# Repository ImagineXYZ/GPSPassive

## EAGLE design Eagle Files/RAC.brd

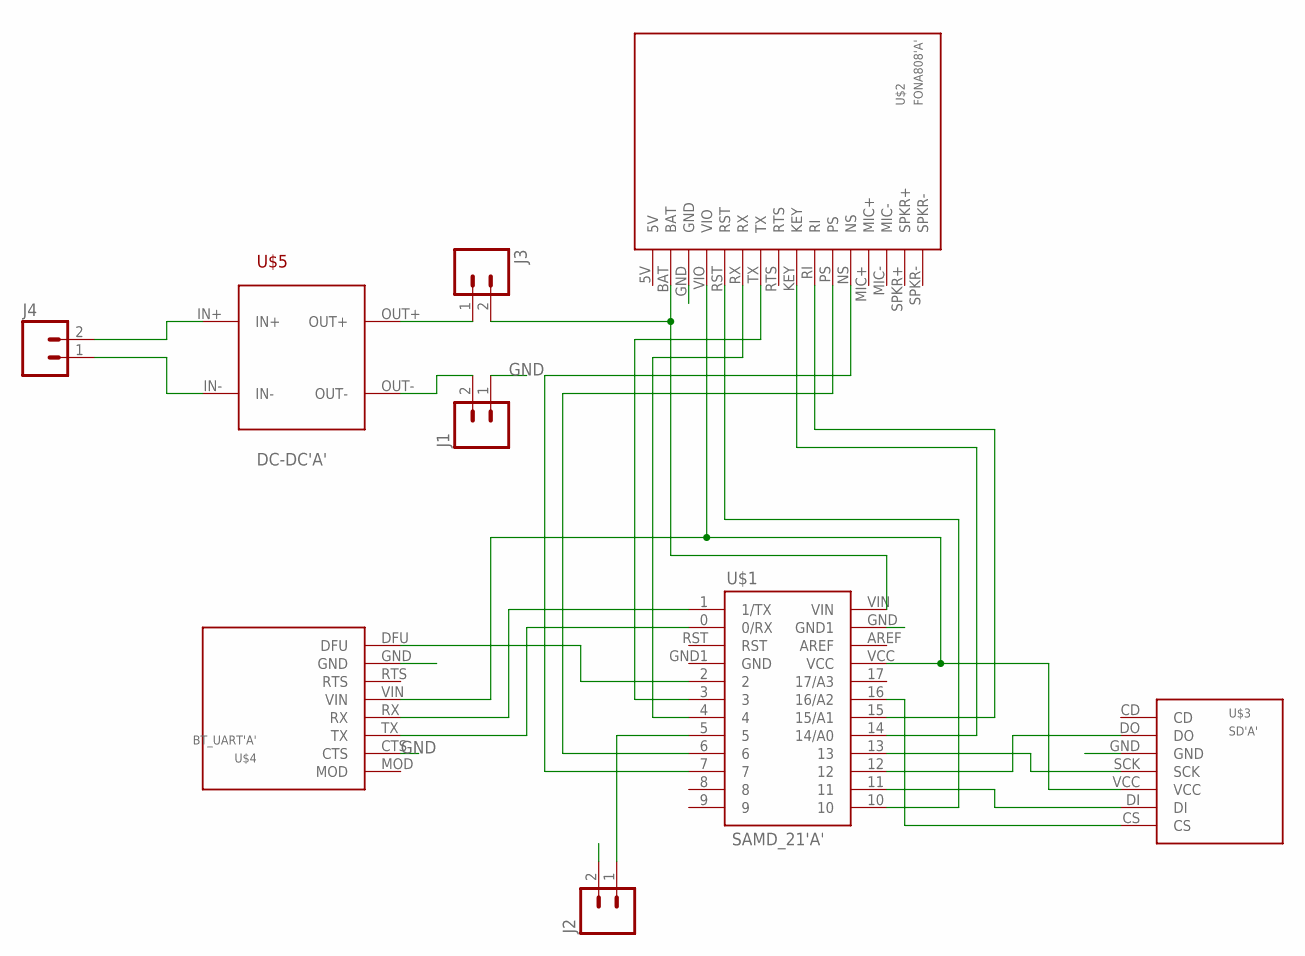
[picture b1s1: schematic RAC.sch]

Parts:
J1, J2, J3: M02PTH; 1X02
J4: M025MM; SCREWTERMINAL-5MM-2
U$1: SAMD_21'A'; MINI
U$2: FONA808'A'; FONA
U$3: SD'A'; SD_BR
U$4: BT_UART'A'; BLE
U$5: DC-DC'A'; DC-DC

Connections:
GND: J1.1, J2.2, U$1.GND (GND1), U$1.GND1 (GND), U$2.GND, U$3.GND, U$4.CTS, U$4.GND
unnamed: J3.2, U$1.VIN, U$2.BAT
unnamed: U$1.4, U$2.RX
unnamed: U$1.3, U$2.TX
unnamed: U$1.VCC, U$2.VIO, U$3.VCC, U$4.VIN
unnamed: U$1.14 (14/A0), U$2.KEY
unnamed: U$1.15 (15/A1), U$2.RI
unnamed: U$1.10, U$2.RST
unnamed: U$1.11, U$3.DI
unnamed: U$1.12, U$3.DO
unnamed: U$1.13, U$3.SCK
unnamed: U$1.16 (16/A2), U$3.CS
unnamed: U$1.0 (0/RX), U$4.TX
unnamed: U$1.2, U$4.DFU
unnamed: J3.1, U$5.OUT+
unnamed: J1.2, U$5.OUT-
unnamed: J4.2, U$5.IN+
unnamed: J4.1, U$5.IN-
S$1: J2.1, U$1.5
S$2: U$1.6, U$2.PS
S$3: U$1.7, U$2.NS
S$4: U$1.1 (1/TX), U$4.RX

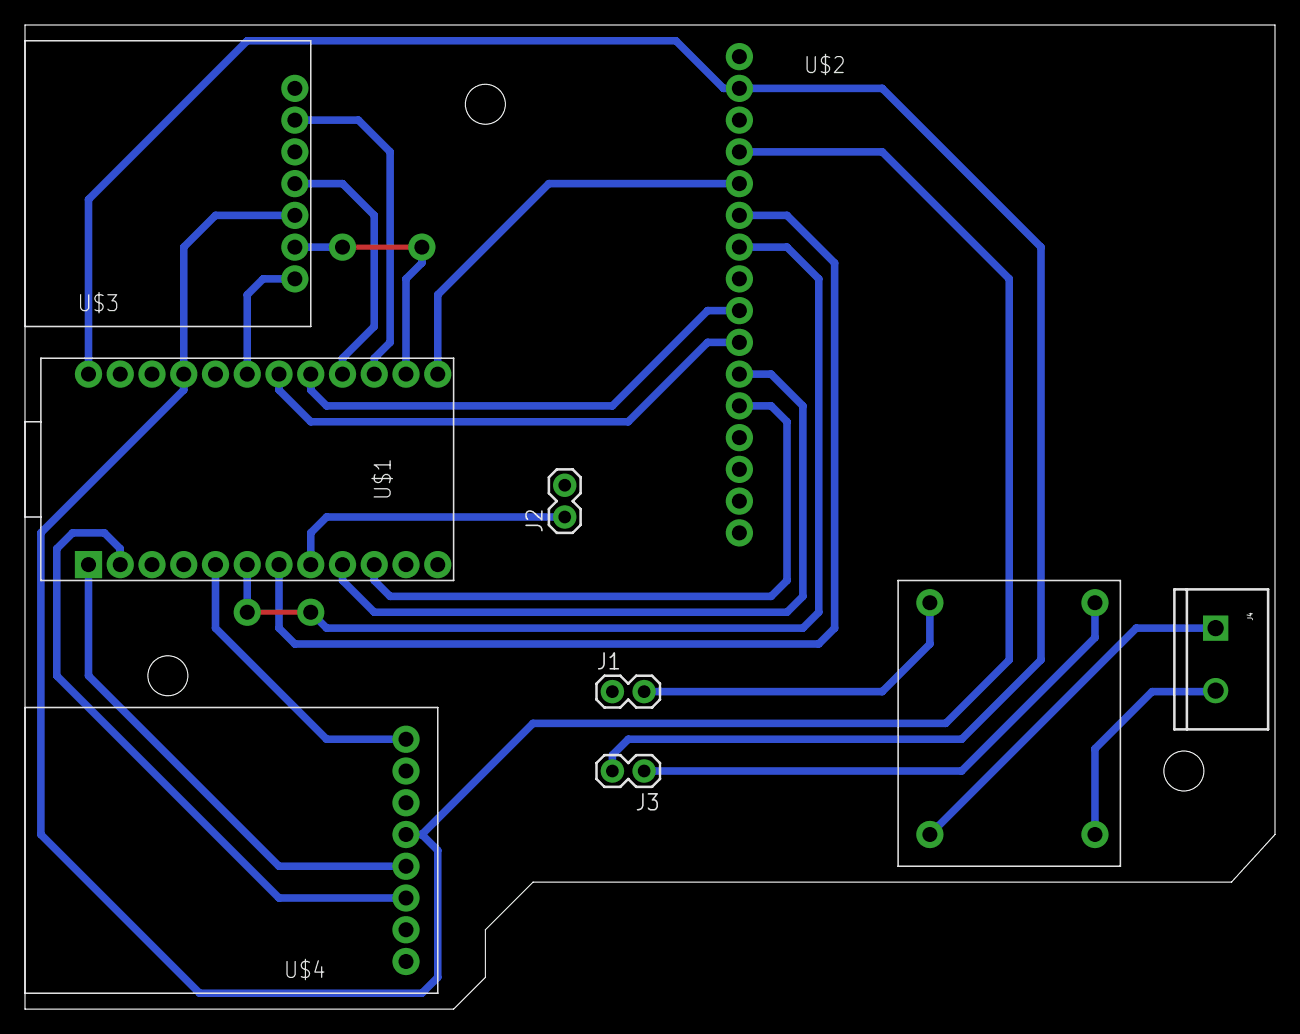
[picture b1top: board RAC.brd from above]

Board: 2 copper layers, 100.0 x 78.7 mm, 9 parts (0 on the bottom side), 22 nets.

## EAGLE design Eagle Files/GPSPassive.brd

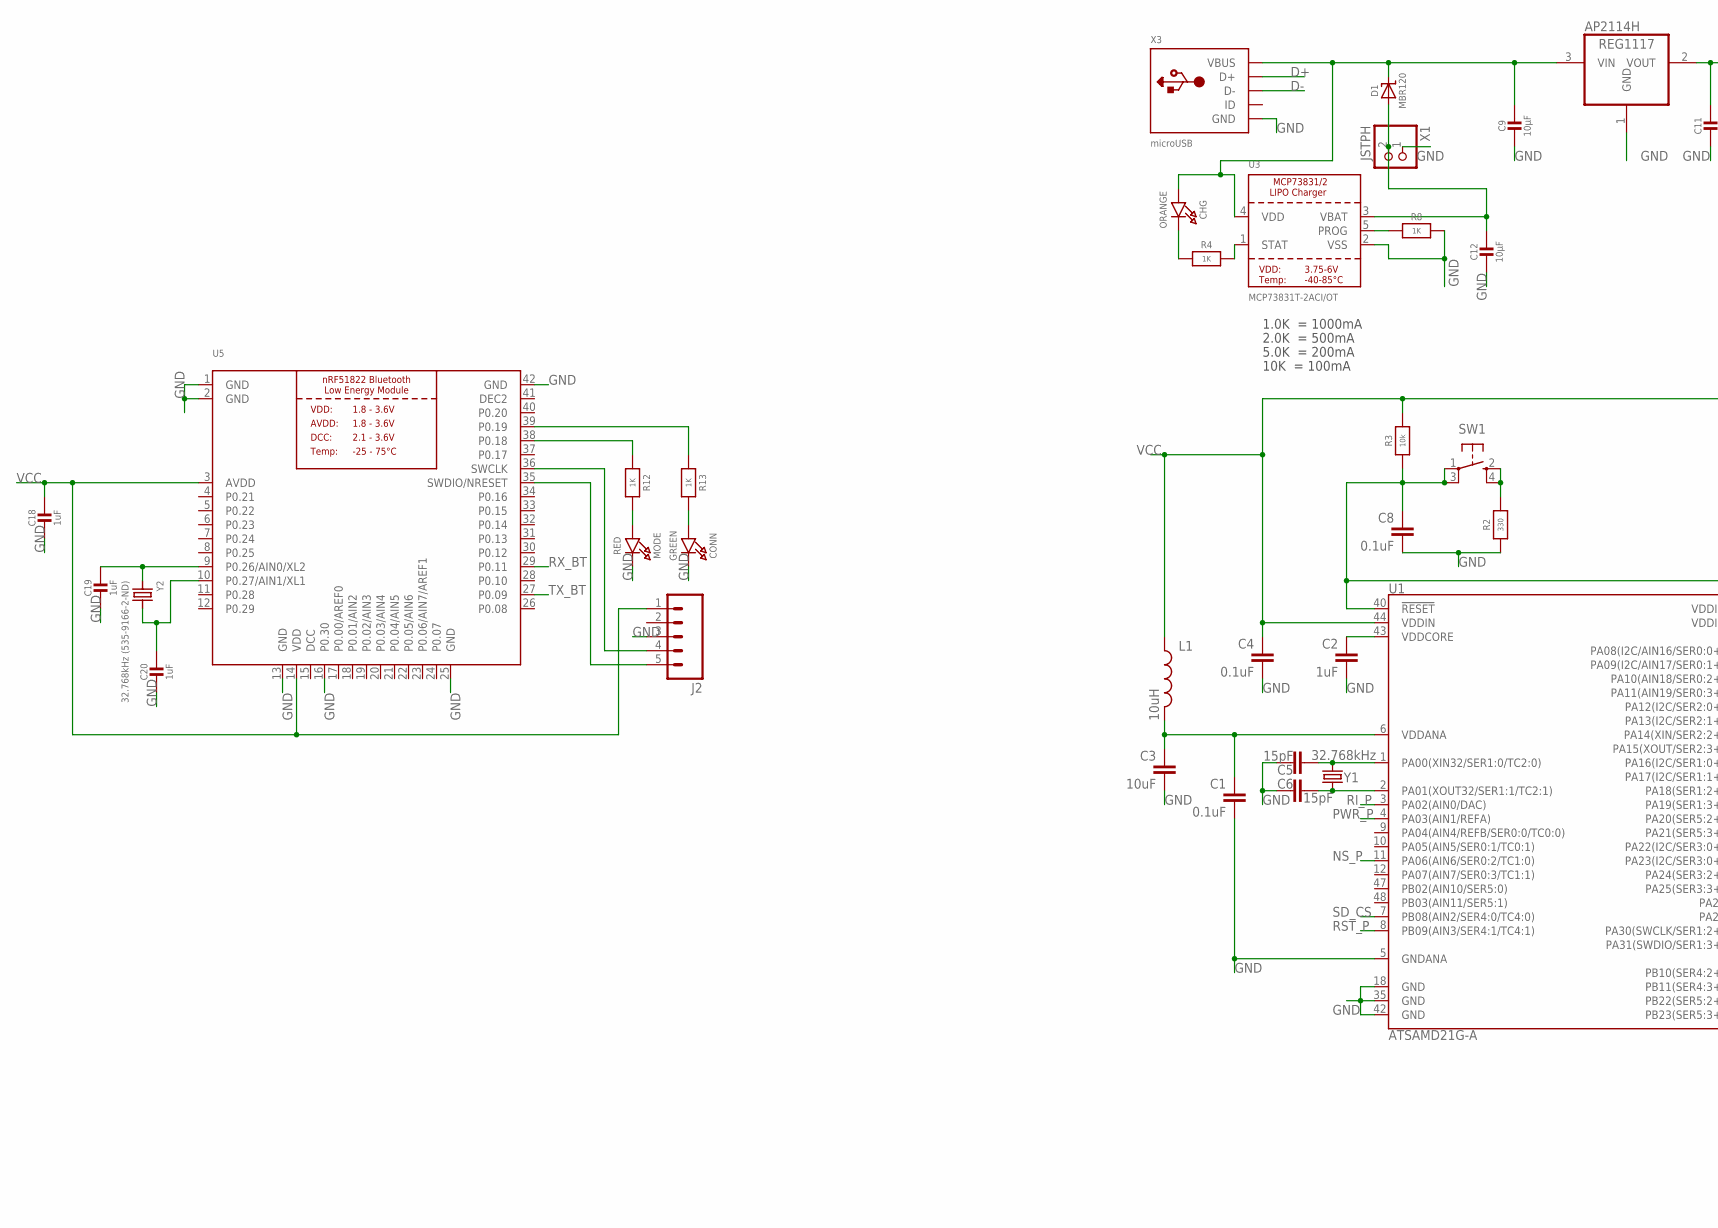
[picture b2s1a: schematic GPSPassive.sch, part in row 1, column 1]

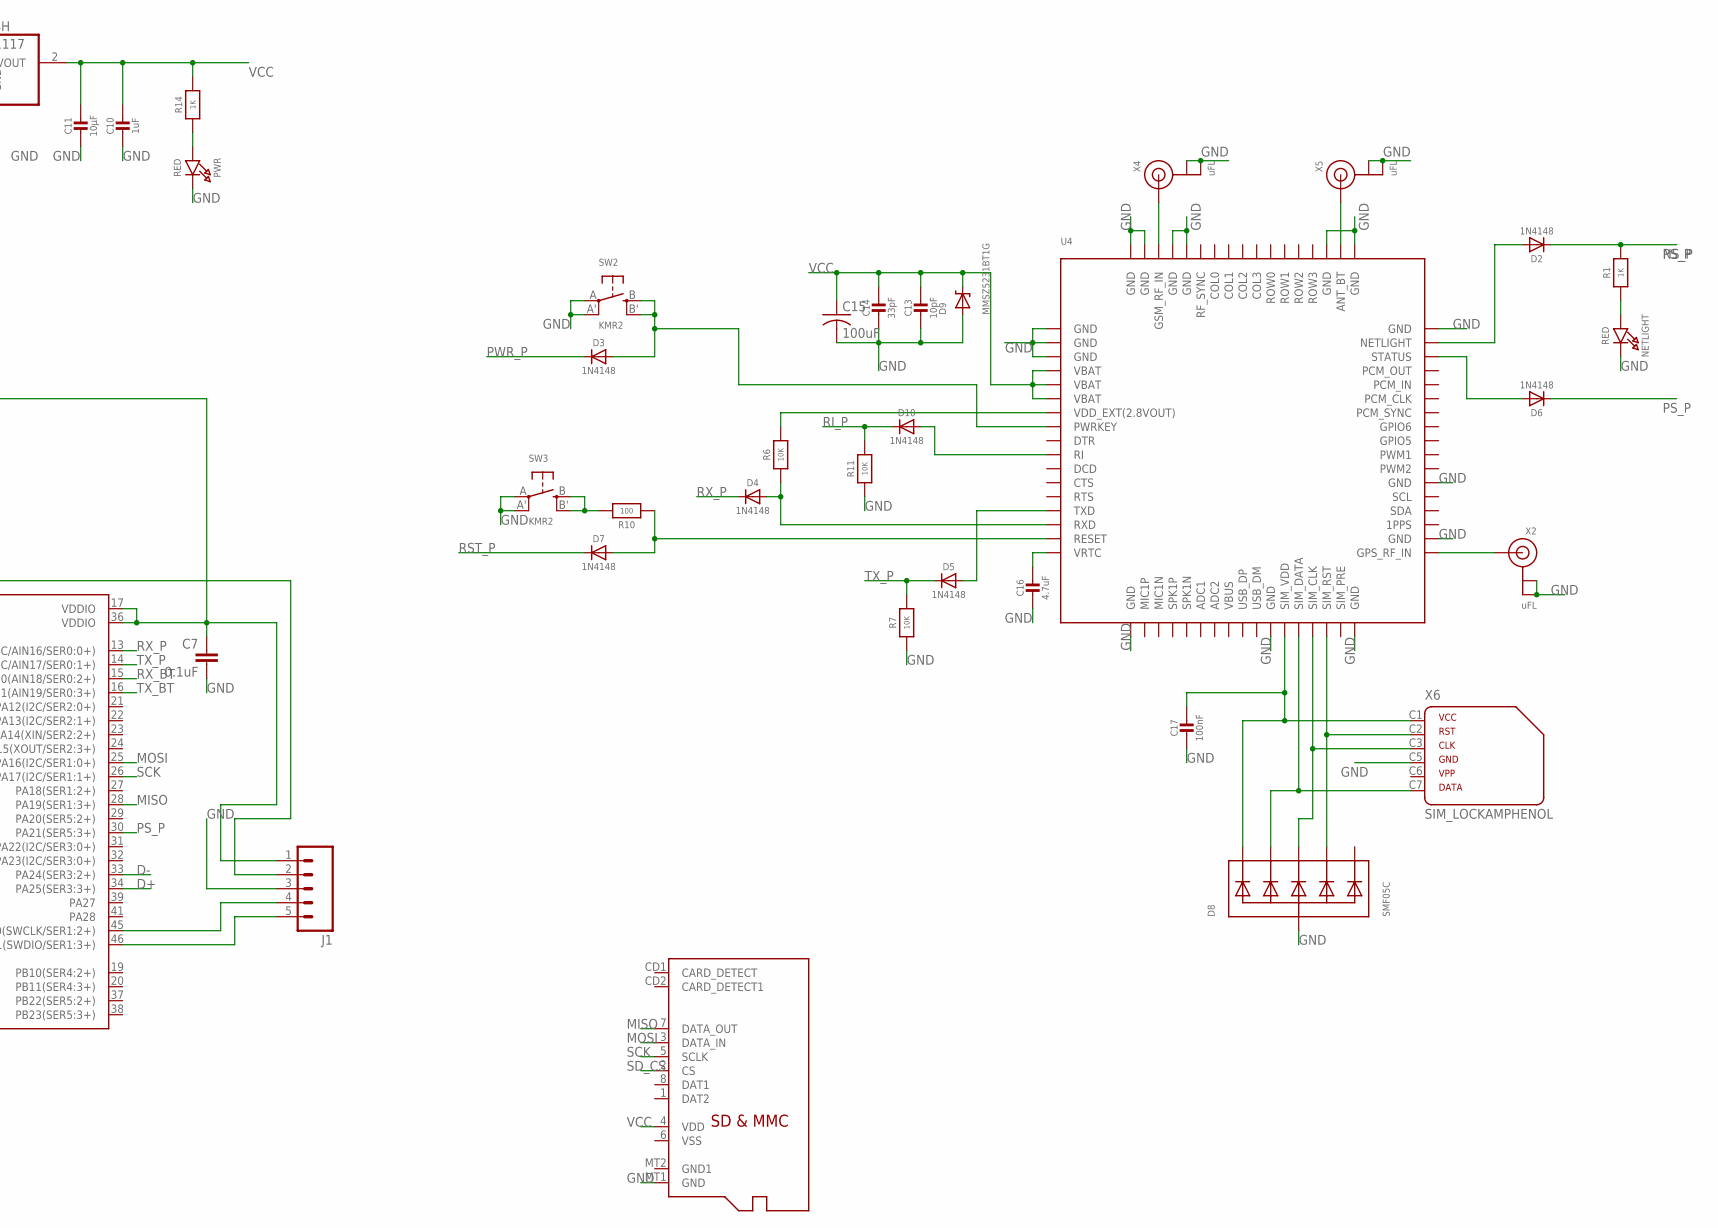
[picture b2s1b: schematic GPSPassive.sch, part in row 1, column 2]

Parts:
AP2114H: REG1117; SOT223
C1, C4, C7, C8: 0.1uF; 0402-CAP
C2: 1uF; 0402-CAP
C3: 10uF; 0402-CAP
C5, C6: 15pF; 0402-CAP
C9, C11, C12: 10µF; 0805-NO
C10: 1uF; 0603-NO
C13: 10pF; 0805-NO
C14: 33pF; 0805-NO
C15: 100uF; C1210
C16: 4.7uF; 0805-NO
C17: 100nF; 0805-NO
C18, C19, C20: 1uF; 0805-NO
CHG: ORANGE; CHIPLED_0805_NOOUTLINE
CONN: GREEN; CHIPLED_0805_NOOUTLINE
D1: MBR120; SOD-123
D2, D3, D4, D5, D6, D7, D10: 1N4148; SOD-323
D8: SMF05C; SOT363
D9: MMSZ5231BT1G; SOD-123
J1, J2: M05PTH; 1X05
L1: 10uH; 0603
MODE: RED; CHIPLED_0805_NOOUTLINE
NETLIGHT: RED; CHIPLED_0805_NOOUTLINE
PWR: RED; CHIPLED_0805_NOOUTLINE
R1, R12, R13, R14: 1K; 0805-NO
R2: 330; 0603-NO
R3: 10k; 0603-NO
R4, R8: 1K; 0603-NO
R6, R7, R11: 10K; 0805-NO
R10: 100; 0805-NO
SW1: SPST_TACT-KMR2; KMR2
SW2, SW3: KMR2; BTN_KMR2_4.6X2.8
U1: ATSAMD21G-A; TQFP-48
U3: MCP73831T-2ACI/OT; SOT23-5
U4: GSM_SIM808_LITERAL; SIM900_SMT
U5: NRF51822_MODULE_MDBT40; BLE_MODULE_RAYTAC_MDBT40
U$1: MICROSD
X1: JSTPH; JSTPH2
X2, X4, X5: uFL; U.FL
X3: microUSB; 4UCONN_20329_V2
X6: SIM_LOCKAMPHENOL; C707_10M006_512_2
Y1: 32.768kHz; CRYSTAL-SMD-3.2X1.5MM
Y2: 32.768kHz (535-9166-2-ND); CRYSTAL_CYL_2X6MM_SMT

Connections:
!RESET: C8.1, J1.2, R3.1, SW1.1, SW1.3 (P1), U1.40 (!RESET!)
CONNECTED_LED: R13.1, U5.39 (P0.19)
D+: U1.34 (PA25(SER3:3+)), X3.D+
D-: U1.33 (PA24(SER3:2+)), X3.D-
DCC: U5.15 (DCC)
DEC2: U5.41 (DEC2)
GND: AP2114H.1 (GND), C1.2, C2.2, C3.2, C4.2, C5.1, C6.2, C7.2, C8.2, C9.2, C10.2, C11.2, C12.2, C13.2, C14.2, C15.2, C16.2, C17.2, C18.2, C19.2, C20.2, CONN.C, D8.2 (A), D9.A, J1.3, J2.3, MODE.C, NETLIGHT.C, PWR.C, R2.1, R7.1, R8.2, R11.1, SW2.A, SW2.A' (P1), SW3.A, SW3.A' (P1), U1.5 (GNDANA), U1.18 (GND), U1.35 (GND), U1.42 (GND), U3.2 (VSS), U4.P$1 (GND), U4.P$2 (GND), U4.P$3 (GND), U4.P$18 (GND), U4.P$28 (GND), U4.P$34 (GND), U4.P$36 (GND), U4.P$40 (GND), U4.P$51 (GND), U4.P$52 (GND), U4.P$54 (GND), U4.P$64 (GND), U4.P$65 (GND), U4.P$67 (GND), U4.P$68 (GND), U5.1 (GND), U5.2 (GND), U5.13 (GND), U5.16 (P0.30), U5.25 (GND), U5.42 (GND), U$1.MT1 (GND), X1.1, X2.1 (GND), X2.2 (GND), X3.BASE@1 (GND), X3.BASE@2 (GND), X3.GND, X3.SPRT@1 (GND), X3.SPRT@2 (GND), X3.SPRT@3 (GND), X3.SPRT@4 (GND), X4.1 (GND), X4.2 (GND), X5.1 (GND), X5.2 (GND), X6.C5 (4)
MISO: U1.28 (PA19(SER1:3+)), U$1.7 (DATA_OUT)
MODE_LED: R12.1, U5.38 (P0.18)
MOSI: U1.25 (PA16(I2C/SER1:0+)), U$1.3 (DATA_IN)
unnamed: C2.1, U1.43 (VDDCORE)
unnamed: C5.2, U1.1 (PA00(XIN32/SER1:0/TC2:0)), Y1.P$2 (2)
unnamed: J1.4, U1.45 (PA30(SWCLK/SER1:2+))
unnamed: C6.1, U1.2 (PA01(XOUT32/SER1:1/TC2:1)), Y1.P$1 (1)
unnamed: J1.5, U1.46 (PA31(SWDIO/SER1:3+))
unnamed: C16.1, U4.P$17 (VRTC)
unnamed: R2.2, SW1.2 (S), SW1.4 (S1)
unnamed: R6.2, U4.P$7 (VDD_EXT(2.8VOUT))
unnamed: C12.1, D1.A, U3.3 (VBAT), X1.2
unnamed: CHG.C, R4.1
unnamed: D4.A, R6.1, U4.P$15 (RXD)
unnamed: R4.2, U3.1 (STAT)
unnamed: R8.1, U3.5 (PROG)
unnamed: AP2114H.3 (VIN), C9.1, CHG.A, D1.C, U3.4 (VDD), X3.VBUS
unnamed: D5.A, U4.P$14 (TXD)
unnamed: D8.5 (C4), U4.P$32 (SIM_RST), X6.C2 (2)
unnamed: D8.4 (C3), U4.P$31 (SIM_CLK), X6.C3 (3)
unnamed: C17.1, D8.1 (C1), U4.P$29 (SIM_VDD), X6.C1 (1)
unnamed: D8.3 (C2), U4.P$30 (SIM_DATA), X6.C7 (6)
unnamed: NETLIGHT.A, R1.1
unnamed: U4.P$66 (GSM_RF_IN), X4.3 (SIGNAL)
unnamed: U4.P$35 (GPS_RF_IN), X2.3 (SIGNAL)
unnamed: D10.A, U4.P$10 (RI)
unnamed: U4.P$53 (ANT_BT), X5.3 (SIGNAL)
unnamed: MODE.A, R12.2
unnamed: CONN.A, R13.2
unnamed: C19.1, U5.9 (P0.26/AIN0/XL2), Y2.1
unnamed: C20.1, U5.10 (P0.27/AIN1/XL1), Y2.2
unnamed: J2.4, U5.36 (SWCLK)
unnamed: J2.5, U5.35 (SWDIO/NRESET)
unnamed: PWR.A, R14.1
NS: D2.A, U4.P$50 (NETLIGHT)
NS_P: D2.C, R1.2, U1.11 (PA06(AIN6/SER0:2/TC1:0))
PS: D6.A, U4.P$49 (STATUS)
PS_P: D6.C, U1.30 (PA21(SER5:3+))
PWRKEY: D3.A, SW2.B (S), SW2.B' (S1), U4.P$8 (PWRKEY)
PWRKEY2: R10.2, SW3.B (S), SW3.B' (S1)
PWR_P: D3.C, U1.4 (PA03(AIN1/REFA))
RI_P: D10.C, R11.2, U1.3 (PA02(AIN0/DAC))
RST: D7.A, R10.1, U4.P$16 (RESET)
RST_P: D7.C, U1.8 (PB09(AIN3/SER4:1/TC4:1))
RX_BT: U1.15 (PA10(AIN18/SER0:2+)), U5.29 (P0.11)
RX_P: D4.C, U1.13 (PA08(I2C/AIN16/SER0:0+))
SCK: U1.26 (PA17(I2C/SER1:1+)), U$1.5 (SCLK)
SD_CS: U1.7 (PB08(AIN2/SER4:0/TC4:0)), U$1.2 (CS)
TX_BT: U1.16 (PA11(AIN19/SER0:3+)), U5.27 (P0.09)
TX_P: D5.C, R7.2, U1.14 (PA09(I2C/AIN17/SER0:1+))
VBUS: U4.P$25 (VBUS)
VCC: AP2114H.2 (VOUT), C4.1, C7.1, C10.1, C11.1, C13.1, C14.1, C15.1, C18.1, D9.C, J1.1, J2.1, L1.1, R3.2, R14.2, U1.17 (VDDIO), U1.36 (VDDIO), U1.44 (VDDIN), U4.P$4 (VBAT), U4.P$5 (VBAT), U4.P$6 (VBAT), U5.3 (AVDD), U5.14 (VDD), U$1.4 (VDD)
VDDANA: C1.1, C3.1, L1.2, U1.6 (VDDANA)

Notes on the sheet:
10K = 100mA
5.0K = 200mA
2.0K = 500mA
1.0K = 1000mA

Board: 2 copper layers, 67 parts (3 on the bottom side), 57 nets, no tracks yet.

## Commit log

2016-07-04 Eagle Files
    Eagle files for GPS passive technology. Uploading.
2016-07-04 Bibliotecas y Código
    Uploading
2016-07-05 Agrega Eagle files actualizados, firmware de prueba, conexiones
2016-07-07 Corrige problemas de espacio entre las pistas para CNC
2016-07-08 Agrega carpetas y documentación para FONA - GSM808
2016-07-09 Estructura inicial de memoria FLash
2016-07-09 Estructura Inicial de memoria SD
2016-07-09 Datos iniciales flash
2016-07-09 Mover Notas a la carpeta docs
2016-07-11 Agrega el esquemático para el SIM808
2016-07-12 Información general de pins y doc de notas
2016-07-12 Corrige el esquemático para el SIM808
2016-07-12 Agrega lista de partes para SIM808
2016-07-12 Actualiza lista de partes
2016-07-12 Creación de readme
2016-07-12 Datos de pines Flash y recomendaciones
2016-07-12 Memoria Flash recomendaciones
2016-07-12 SIMCOM
    Agrega link de proveedror de SIMCOM
2016-07-12 Documento de Flash, conflicto merge solucion
2016-07-12 Incluir archivo MemoriaFlash resolviendo conflicto
2016-07-12 Datos Flash mem y CFI tables
2016-07-12 Crea carpeta para SAMD21
2016-07-12 Agrega SIM808
2016-07-12 Bluetooth
    Agrega documentos relacionados con el Bluetooth
2016-07-19 Agrega esquemático para SAMD21
2016-07-19 Agrega JTAG a SAMD21
2016-07-19 Corrige error en tierra de JTAG para SAMD21
2016-07-28 Corrige error en regulador, amplía pads
2016-07-29 Actualiza la biblioteca para RAC
2016-08-12 Agrega cambios en el .brd
2016-08-12 Agrega antena para BT en SIM808
2016-08-13 Agrega manual de referencia de nRF51
2016-08-13 Agrega esquemático para todos los sub módulos
2016-08-17 Agrega esquemático para nRF51822
2016-08-17 Corrige error en ID de pines ADC
2016-08-18 Agrega board principal
2016-08-19 Corrige error en asignación de pines
2016-08-19 Cambia el ancho de pistas a 0.6096mm
2016-08-20 Corrige colocación de LED
2016-08-23 Flash memory smd Footprint Eagle Device, DS Part, DS Breakout
2016-08-26 Pines de acuerdo al mas reciente archivo de Eagle
    Cambio en la asignación de pines
2016-08-26 Corrige inversión de pines TX y RX para BLE
2016-08-26 Agrega detalles sobre pin 16
2016-08-26 Agrega archivo de debug para pcb
2016-08-30 Modificaciones lógica BLE y debug flag
    Se aumenta el buffer de recepción del BLE, delay en el envío del BLE
    para evitar conflictos en la RAM del bluetooth y bandera de control para
    el debugging, condicional en loop principal para ble.avalaible
2016-08-30 Flag Debug en el init del Serial.
2016-08-31 Breakout board memoria FLASH
2016-09-02 Prueba Flash Arduino
2016-09-02 Valores umbrales
2016-09-02 Bandera de debug y otros docs
    Bandera para debug con GPRS, Build of materials y SIM/SD holder docs
2016-09-02 Debug Flag
    Identación
2016-09-08 Componentes nuevos en el BOM
    Carpetas de FONA y SD
2016-09-23 Mejora de algoritmo BT
2016-09-30 Fotos de los avances
    Pics
2016-09-30 Completa protocolo de BT
2016-10-07 Agrega diagrama de secuencia del protocolo para BT
2016-10-20 Serial Port
    Setup
2016-10-27 Agrega función de hash y lectura de archivos
2016-12-01 Agrega pruebas iniciales para geofencing
2016-12-06 Agrega algoritmo crossing number
2016-12-15 Agrega biblioteca para quadtree
2017-01-14 Agrega pruebas de quadtree
2017-01-14 Agrega documentación RockBLOCK

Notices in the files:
parts and their libraries:
SparkFun-Capacitors: Licensing: Creative Commons ShareAlike 4.0 International - https://creativecommons.org/licenses/by-sa/4.0
microbuilder: This work is placed in the public domain, and may be freely used for commercial and non-commercial work with the following conditions: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
